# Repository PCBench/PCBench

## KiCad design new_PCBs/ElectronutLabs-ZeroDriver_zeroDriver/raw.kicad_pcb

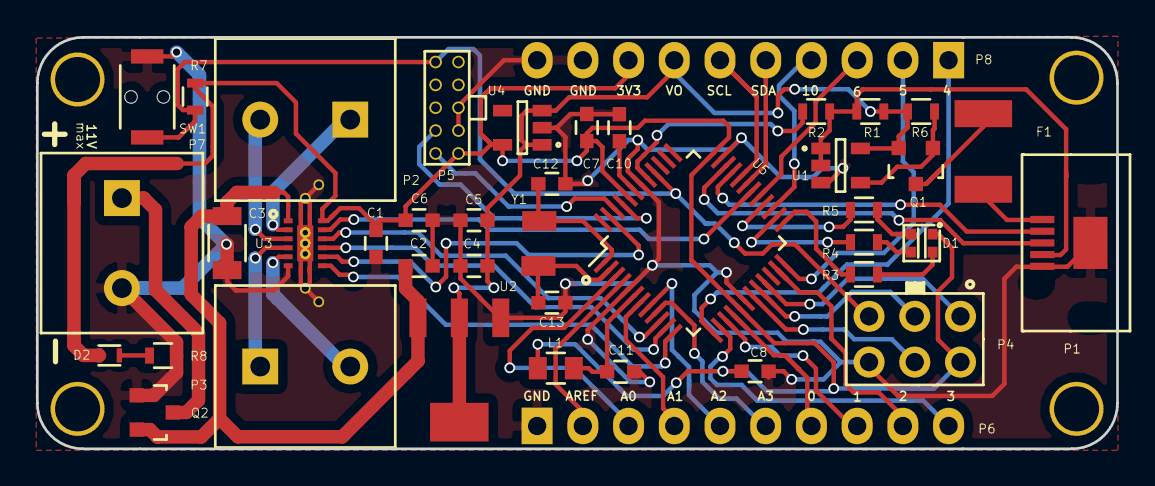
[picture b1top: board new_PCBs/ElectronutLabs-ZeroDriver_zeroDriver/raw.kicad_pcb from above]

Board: 2 copper layers, 60.0 x 22.9 mm, 48 parts (1 on the bottom side), 53 nets.

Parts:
C1, C2, C7, C8, C10, C11: 0.1uF; C_0603
C3: 10uF; C_1206
C4: 10uF; C_0603
C5: 1uF; C_0603
C6: 2.2uF; C_0603
C12, C13: 15pF; C_0603
D1: Led_RGB_CA; CREE-CA
D2: RED LED; LED_0606
F1: FUSE; BOURNS_PTC_FUSE_S1
L1: Ferrite Bead; C_0805
P1: USB_OTG
P2: M1; TerminalBlock_5mm_1x2
P3: M2; TerminalBlock_5mm_1x2
P4: ICSP; ICSP_2x3
P5: CONN_02X05; JTAG
P6, P8: CONN_01X10; Pin_Header_Straight_1x10
P7: M3; TerminalBlock_5mm_1x2
Q1: DMG2307L; SOT-23
Q2: NCE3407A; SOT-23
R1: 100K; R_0603
R2: 300R; R_0603
R3: 200; R_0603
R4, R5: 100; R_0603
R6: 47K; R_0603
R7: 10K; R_0603
R8: 330R; R_0603
SW1: SW_PUSH; peter-switch
U1: 74AHC1G125; SOT-23-5
U2: LD1117S5TR; LD1117_SOT223
U3: DRV8835
U4: AP2112K; SOT-23-5
U5: SAMD21G18A; TQFP-48_7x7mm_Pitch0.5mm
Y1: 32.768kHz; crystal
via: VAL**; via
via#2, via#3, via#4, via#5, via#6, via#7: VAL**; via

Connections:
0: P6.7, U5.16
1: P6.8, U5.15
2: P6.9, U5.23
3: P6.10, U5.14
3V3: C1.1, C6.1, C7.1, C8.2, D1.1, D2.2, L1.1, P4.2, P5.1, P8.8, R7.1, U3.12, U4.5, U5.17, U5.36, U5.44
4: P8.1, U5.13
5: P8.2, U5.24
6: P8.3, U5.29
10: P8.4, U5.27
A0: P6.3, U5.3
A1: P6.4, U5.7
A2: P6.5, U5.8
A3: P6.6, U5.9
AREF: P6.2, U5.4
BLUE: R4.2, U5.26
D+: P1.3, U5.34
D-: P1.2, U5.33
GND: C1.2, C2.2, C3.2, C4.2, C5.2, C6.2, C7.2, C8.1, C10.1, C11.1, C12.1, C13.1, P1.5, P1.6, P4.6, P5.3, P5.5, P6.1, P7.2, P8.9, P8.10, Q2.1, R8.2, SW1.2, U1.3, U2.1, U3.6, U4.2, U5.5, U5.18, U5.35, U5.42
GREEN: R3.2, U5.25
ID: P1.4, R1.2, R2.1, U1.1, U1.2
MISO: P4.1, U5.21
MODE: U3.11, U5.30
MOSI: P4.4, U5.19
unnamed: C10.2, U5.43
unnamed: C11.2, L1.2, U5.6
unnamed: C12.2, U5.1, Y1.1
unnamed: C13.2, U5.2, Y1.2
unnamed: D1.2, R3.1
unnamed: D1.3, R4.1
unnamed: D1.4, R5.1
unnamed: D2.1, R8.1
unnamed: F1.1, P1.1
unnamed: F1.2, Q1.3
unnamed: P2.1, U3.2
unnamed: P2.2, U3.3
unnamed: P3.1, U3.4
unnamed: P3.2, U3.5
unnamed: Q1.1, R6.2, U1.4
PH1: U3.10, U5.10
PH2: U3.8, U5.47
PWM1: U3.9, U5.11
PWM2: U3.7, U5.12
RED: R5.2, U5.28
RESET: P4.5, P5.10, R7.2, SW1.1, U5.40
SCK: P4.3, U5.20
SCL: P8.6, U5.32
SDA: P8.5, U5.31
SWCLK: P5.4, U5.45
SWDIO: P5.2, U5.46
USB: R2.2, U5.41
VM: P7.1, Q2.3
VM+: C2.1, C3.1, Q2.2, U2.3, U3.1
VO: C4.1, C5.1, P8.7, Q1.2, R1.1, R6.1, U1.5, U2.2, U4.1, U4.3

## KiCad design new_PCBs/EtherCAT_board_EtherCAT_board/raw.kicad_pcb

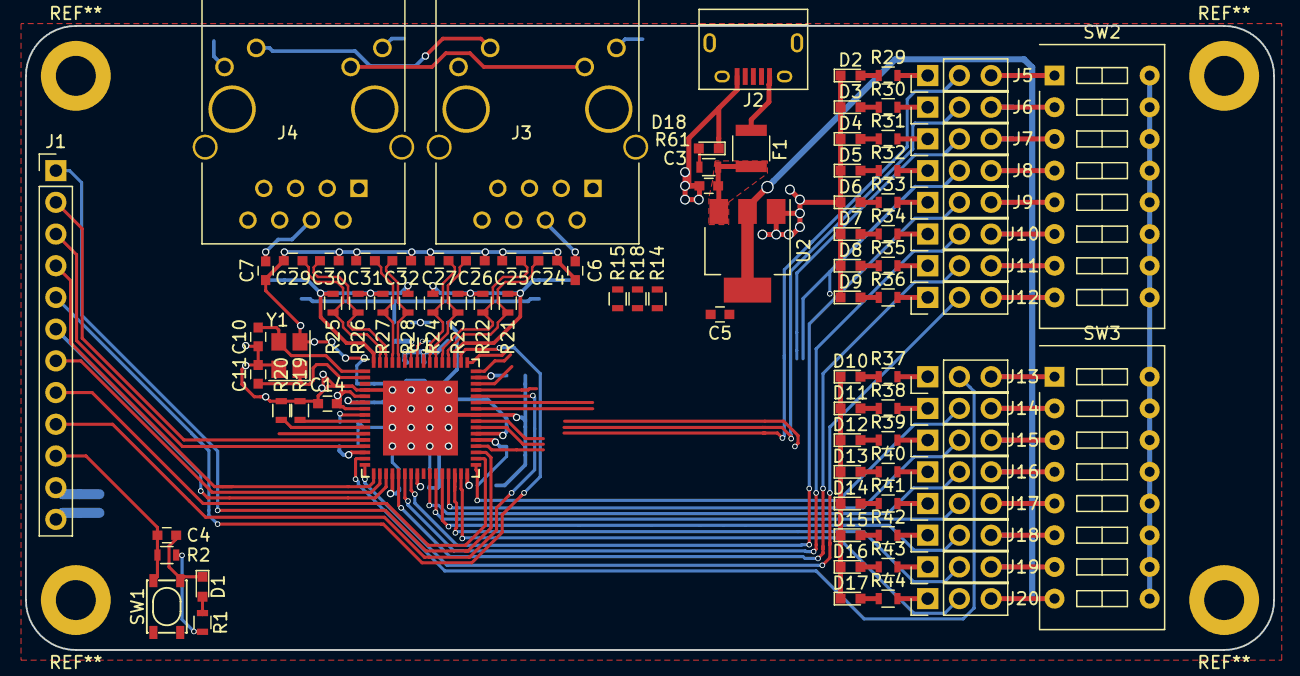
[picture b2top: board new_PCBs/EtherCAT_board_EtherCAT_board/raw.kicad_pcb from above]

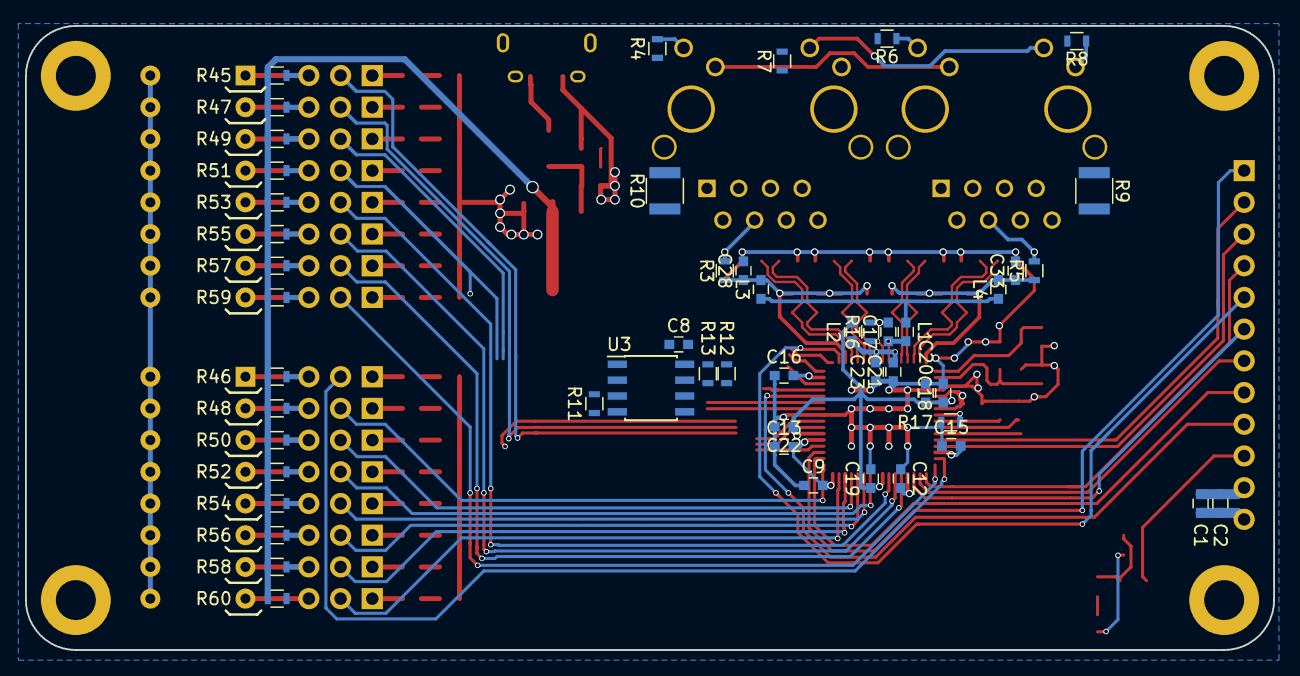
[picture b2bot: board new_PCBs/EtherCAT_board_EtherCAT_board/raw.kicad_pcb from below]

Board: 2 copper layers, 100.0 x 50.0 mm, 144 parts (51 on the bottom side), 112 nets.

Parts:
C1, C2, C5: 22u; C_0603
C3: 10u; C_0603
C4, C8, C9, C12, C13, C14, C15, C16, C17, C20, C21, C22, C23, C28, C33: 0.1u; C_0603
C6, C7: 0.022u; C_0603
C10, C11, C24, C25, C26, C27, C29, C30, C31, C32: 10p; C_0603
C18: 1u; C_0603
C19: 470p; C_0603
D1, D2, D3, D4, D5, D6, D7, D8, D9, D10, D11, D12, D13, D14, D15, D16, D17, D18: LED; LED_0603
F1: Fuse; R_1210
J1: CONN_01X12; Pin_Header_Straight_1x12_Pitch2.54mm
J2: USB_OTG; USB_Micro-B
J3, J4: RJ45-PULSETRANS; RJ45_J0011D21BNL
J5, J6, J7, J8, J9, J10, J11, J12, J13, J14, J15, J16, J17, J18, J19, J20: CONN_01X03; Pin_Header_Straight_1x03_Pitch2.54mm
L1, L2, L3, L4: 220; C_0603
R1, R29, R30, R31, R32, R33, R34, R35, R36, R37, R38, R39, R40, R41, R42, R43, R44, R61: 1k; R_0603
R2, R14, R15, R17, R18, R19, R20, R45, R46, R47, R48, R49, R50, R51, R52, R53, R54, R55, R56, R57, R58, R59, R60: 10k; R_0603
R3, R5: 0; R_0603
R4, R6, R7, R8: 330; R_0603
R9, R10: 0; R_1210
R11, R12, R13: 4.7k; R_0603
R16: 12.1k; R_0603
R21, R22, R23, R24, R25, R26, R27, R28: 49.9; R_0603
SW1: SKRPACE010; ALPS_SKRPAxE010
SW2, SW3: DIP_SW_8P; SW_DIP_x8_W7.62mm_Slide
U1: LAN9252; QFN-64-1EP_9x9mm_Pitch0.5mm_LAN9252
U2: LM1117-3.3; SOT-223-3Lead_TabPin2
U3: 24LC512; SOIC-8_3.9x4.9mm_Pitch1.27mm
Y1: Crystal_GND24; Crystal_SMD_Abracon_ABM8G-4pin_3.2x2.5mm

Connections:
+3V3: C1.1, C2.1, C5.1, C8.2, C9.2, C12.2, C13.2, C14.2, C15.2, C16.2, J1.11, L1.1, L3.1, L4.1, R1.2, R2.2, R7.2, R8.2, R12.1, R13.1, R14.2, R45.1, R46.1, R47.1, R48.1, R49.1, R50.1, R51.1, R52.1, R53.1, R54.1, R55.1, R56.1, R57.1, R58.1, R59.1, R60.1, U1.5, U1.7, U1.14, U1.20, U1.32, U1.37, U1.47, U2.2, U3.8
+5V: C3.1, F1.1, R61.2, U2.3
/LAN9252/LINKACTLED0: R4.2, R15.1, U1.48
/LAN9252/LINKACTLED1: R6.2, R18.1, U1.46
/LAN9252/RUNLED: J3.11, J4.11, R14.1, U1.45
/LAN9252/VDD33TXRX1: C28.1, L3.2, R3.1, R21.1, R22.1, R23.1, R24.1, U1.51
/LAN9252/VDD33TXRX2: C33.1, L4.2, R5.1, R25.1, R26.1, R27.1, R28.1, U1.64
/RX1_N: C26.1, J3.6, R23.2, U1.54
/RX1_P: C27.1, J3.3, R24.2, U1.55
/RX2_N: C31.1, J4.6, R27.2, U1.61
/RX2_P: C32.1, J4.3, R28.2, U1.60
/TX1_N: C24.1, J3.2, R21.2, U1.52
/TX1_P: C25.1, J3.1, R22.2, U1.53
/TX2_N: C29.1, J4.2, R25.2, U1.63
/TX2_P: C30.1, J4.1, R26.2, U1.62
GND: C1.2, C2.2, C3.2, C4.1, C5.2, C6.1, C7.1, C8.1, C9.1, C10.1, C11.2, C12.1, C13.1, C14.1, C15.1, C16.1, C17.2, C18.2, C19.2, C20.2, C21.1, C22.2, C23.1, C24.2, C25.2, C26.2, C27.2, C28.2, C29.2, C30.2, C31.2, C32.2, C33.2, D1.1, D2.1, D3.1, D4.1, D5.1, D6.1, D7.1, D8.1, D9.1, D10.1, D11.1, D12.1, D13.1, D14.1, D15.1, D16.1, D17.1, D18.1, J1.12, J2.5, J2.6, J3.10, J4.10, R9.2, R10.2, R11.2, R15.2, R16.2, R17.1, R18.2, R19.2, R20.1, SW1.4, SW2.9, SW2.10, SW2.11, SW2.12, SW2.13, SW2.14, SW2.15, SW2.16, SW3.9, SW3.10, SW3.11, SW3.12, SW3.13, SW3.14, SW3.15, SW3.16, U1.4, U1.41, U1.65, U2.1, U3.4, Y1.2, Y1.4
GNDPWR: J3.8, J3.13, J3.14, J4.8, J4.13, J4.14, R9.1, R10.1
GPIO0: J5.2, U1.36
GPIO1: J6.2, U1.39
GPIO2: J7.2, U1.40
GPIO3: J8.2, U1.49
GPIO4: J9.2, U1.23
GPIO5: J10.2, U1.22
GPIO6: J11.2, U1.21
GPIO7: J12.2, U1.16
GPIO8: J13.2, U1.15
GPIO9: J14.2, U1.33
GPIO10: J15.2, U1.29
GPIO11: J16.2, U1.26
GPIO12: J17.2, U1.27
GPIO13: J18.2, U1.28
GPIO14: J19.2, U1.30
GPIO15: J20.2, U1.31
IN_DGIO0: J5.3, R45.2, SW2.1
IN_DGIO1: J6.3, R47.2, SW2.2
IN_DGIO2: J7.3, R49.2, SW2.3
IN_DGIO3: J8.3, R51.2, SW2.4
IN_DGIO4: J9.3, R53.2, SW2.5
IN_DGIO5: J10.3, R55.2, SW2.6
IN_DGIO6: J11.3, R57.2, SW2.7
IN_DGIO7: J12.3, R59.2, SW2.8
IN_DGIO8: J13.3, R46.2, SW3.1
IN_DGIO9: J14.3, R48.2, SW3.2
IN_DGIO10: J15.3, R50.2, SW3.3
IN_DGIO11: J16.3, R52.2, SW3.4
IN_DGIO12: J17.3, R54.2, SW3.5
IN_DGIO13: J18.3, R56.2, SW3.6
IN_DGIO14: J19.3, R58.2, SW3.7
IN_DGIO15: J20.3, R60.2, SW3.8
IRQ: J1.9, U1.44
LATCH0: J1.8, U1.34
LATCH1: J1.7, U1.18
unnamed: C6.2, J3.4, J3.5, R3.2
unnamed: C7.2, J4.4, J4.5, R5.2
unnamed: C10.2, U1.1, Y1.3
unnamed: C11.1, U1.2, Y1.1
unnamed: C17.1, L1.2, U1.58
unnamed: C18.1, C19.1, C20.1, C22.1, L2.2, U1.6, U1.24, U1.38
unnamed: C21.2, C23.2, L2.1, U1.56, U1.59
unnamed: D1.2, R1.1
unnamed: D2.2, R29.1
unnamed: D3.2, R30.1
unnamed: D4.2, R31.1
unnamed: D5.2, R32.1
unnamed: D6.2, R33.1
unnamed: D7.2, R34.1
unnamed: D8.2, R35.1
unnamed: D9.2, R36.1
unnamed: D10.2, R37.1
unnamed: D11.2, R38.1
unnamed: D12.2, R39.1
unnamed: D13.2, R40.1
unnamed: D14.2, R41.1
unnamed: D15.2, R42.1
unnamed: D16.2, R43.1
unnamed: D17.2, R44.1
unnamed: D18.2, R61.1
unnamed: F1.2, J2.1
unnamed: J3.9, R4.1
unnamed: J3.12, R7.1
unnamed: J4.9, R6.1
unnamed: J4.12, R8.1
unnamed: R11.1, U3.1, U3.2, U3.3, U3.7
unnamed: R12.2, U1.42, U3.5
unnamed: R13.2, U1.43, U3.6
unnamed: R16.1, U1.57
unnamed: R17.2, U1.8
unnamed: R19.1, U1.9
unnamed: R20.2, U1.10
OUT_DGIO0: J5.1, R29.2
OUT_DGIO1: J6.1, R30.2
OUT_DGIO2: J7.1, R31.2
OUT_DGIO3: J8.1, R32.2
OUT_DGIO4: J9.1, R33.2
OUT_DGIO5: J10.1, R34.2
OUT_DGIO6: J11.1, R35.2
OUT_DGIO7: J12.1, R36.2
OUT_DGIO8: J13.1, R37.2
OUT_DGIO9: J14.1, R38.2
OUT_DGIO10: J15.1, R39.2
OUT_DGIO11: J16.1, R40.2
OUT_DGIO12: J17.1, R41.2
OUT_DGIO13: J18.1, R42.2
OUT_DGIO14: J19.1, R43.2
OUT_DGIO15: J20.1, R44.2
RESET: C4.2, J1.10, R2.1, SW1.2, U1.11
SCK: J1.6, U1.19
SI/SIO0: J1.4, U1.17
SIO2: J1.2, U1.12
SIO3: J1.1, U1.35
SO/SIO1: J1.3, U1.13
~SCS: J1.5, U1.50

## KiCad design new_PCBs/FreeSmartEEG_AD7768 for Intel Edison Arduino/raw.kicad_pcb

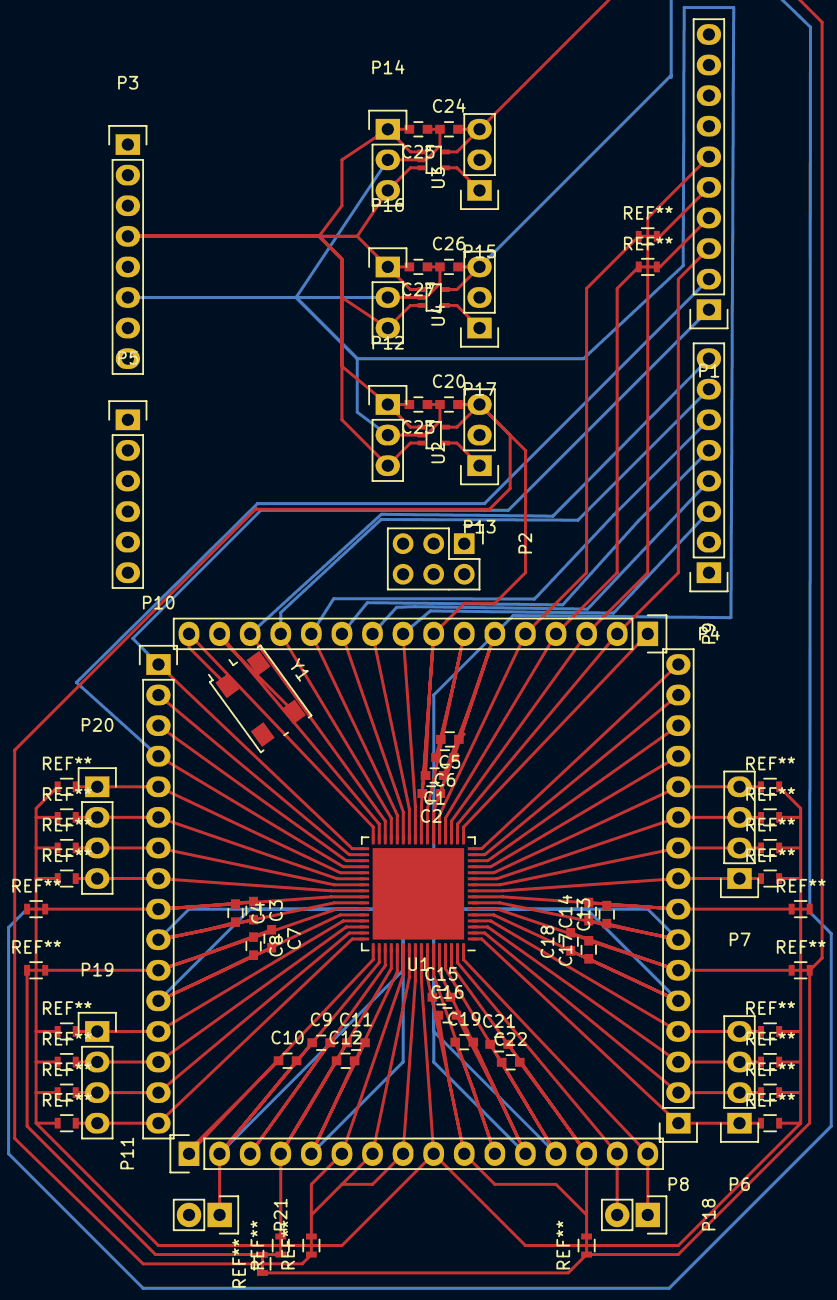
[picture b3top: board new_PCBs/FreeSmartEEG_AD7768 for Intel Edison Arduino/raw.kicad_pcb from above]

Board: 2 copper layers, 53 parts (0 on the bottom side), 50 nets.

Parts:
C1, C5, C13, C17: C 1uF; C_0603
C2, C3, C6, C7, C9, C10, C11, C14, C15, C18, C19, C21: 100pF; C_0603
C4, C8, C12, C16, C20, C22, C23, C24, C25, C26, C27: 1uF; C_0603
P1: DIGITAL(_PWM); Pin_Header_Straight_1x10
P2: ICSP; Pin_Header_Straight_2x03
P3: POWER; Pin_Header_Straight_1x08
P4: DIGITAL(_PWM); Pin_Header_Straight_1x08
P5: ANALOG_IN; Pin_Header_Straight_1x06
P6: AIN01; Pin_Header_Straight_1x04
P7: AIN23; Pin_Header_Straight_1x04
P8, P9, P10, P11: CONN_01X16; Pin_Header_Straight_1x16
P12, P13, P14, P15, P16, P17: CONN_01X03; Pin_Header_Straight_1x03
P18: AUXAIN; Pin_Header_Straight_1x02
P19: AIN45; Pin_Header_Straight_1x04
P20: AIN67; Pin_Header_Straight_1x04
P21: GNDAIN; Pin_Header_Straight_1x02
U1: AD7779; LFCSP-64-1EP_9x9mm_Pitch0.5mm
U2, U3: LP5907QMFX-3.3Q1; SC-70-5
U4: LP5907QMFX-2.5Q1; SC-70-5
Y1: 8.192 MHz; SMD0503_4P_Crystal

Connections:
3.3V: C23.2, C25.2, C27.2, P3.4, P12.1, P12.3, P14.1, P14.3, P16.1, P16.3, U2.1, U2.3, U3.1, U3.3, U4.1, U4.3
5V: P2.2, P3.5
ADC_RESET: P1.2, P10.4, U1.36
AIN0+: P6.2, P8.2, U1.2
AIN0-: P6.1, P8.1, U1.1
AIN1+: P6.4, P8.4, U1.4
AIN1-: P6.3, P8.3, U1.3
AIN2+: P7.2, P8.10, U1.10
AIN2-: P7.1, P8.9, U1.9
AIN3+: P7.4, P8.12, U1.12
AIN3-: P7.3, P8.11, U1.11
AIN4+: P10.15, P19.3, U1.47
AIN4-: P10.16, P19.4, U1.48
AIN5+: P10.13, P19.1, U1.45
AIN5-: P10.14, P19.2, U1.46
AIN6+: P10.7, P20.3, U1.39
AIN6-: P10.8, P20.4, U1.40
AIN7+: P10.5, P20.1, U1.37
AIN7-: P10.6, P20.2, U1.38
ALERT: P8.16, U1.16
AREF: P1.8, P3.1
AUXAIN+: P11.15, P18.2, U1.63
AUXAIN-: P11.16, P18.1, U1.64
AVDD: C7.1, C8.1, C11.1, C12.1, C15.1, C16.1, C17.2, C18.2, C21.2, C22.2, C24.2, P8.6, P10.11, P11.4, P11.10, P11.14, P15.3, U1.6, U1.43, U1.52, U1.58, U1.62, U3.5
AVSS: C1.1, C2.1, C3.2, C4.2, C5.1, C6.1, C7.2, C8.2, C9.1, C10.2, C11.2, C12.2, C13.1, C14.1, C15.2, C16.2, C17.1, C18.1, C19.2, C20.1, C21.1, C22.1, C23.1, C24.1, C25.1, C26.1, C27.1, P1.7, P2.6, P3.6, P3.7, P8.5, P8.7, P9.6, P10.10, P10.12, P11.2, P11.5, P11.12, P11.13, P12.2, P14.2, P16.2, P21.1, P21.2, U1.5, U1.7, U1.22, U1.42, U1.44, U1.50, U1.53, U1.60, U1.61, U1.65, U2.2, U3.2, U4.2
CLK_SEL: C1.2, C2.2, C20.2, P9.1, P9.8, P11.6, P11.7, P11.8, P13.3, U1.17, U1.24, U1.54, U1.55, U1.56, U2.5
CS: P1.3, P9.2, U1.18
DCLK: P4.7, P9.13, U1.29
DOUT0: P4.6, P9.12, U1.28
DOUT1: P4.5, P9.11, U1.27
DOUT2: P4.4, P9.10, U1.26
DOUT3: P4.3, P9.9, U1.25
DRDY: P4.8, P9.14, U1.30
GPIO0: P8.13, U1.13
GPIO1: P8.14, U1.14
GPIO2: P8.15, U1.15
MISO: P1.5, P9.5, U1.21
MOSI: P1.4, P9.4, U1.20
unnamed: C5.2, C6.2, U1.23
unnamed: C9.2, U1.51
unnamed: C19.1, U1.59
OUT_VREF: C3.1, C4.1, C13.2, C14.2, C26.2, P8.8, P10.9, P17.3, U1.8, U1.41, U4.5
REF_OUT: C10.1, P11.1, U1.49
SCLK: P1.6, P9.3, U1.19
START: P1.1, P10.1, U1.33
SYNC_IN: P10.3, U1.35
SYNC_OUT: P10.2, U1.34
VCM: P11.9, U1.57
XTAL1: P9.15, U1.31, Y1.2
XTAL2: P9.16, U1.32, Y1.1
